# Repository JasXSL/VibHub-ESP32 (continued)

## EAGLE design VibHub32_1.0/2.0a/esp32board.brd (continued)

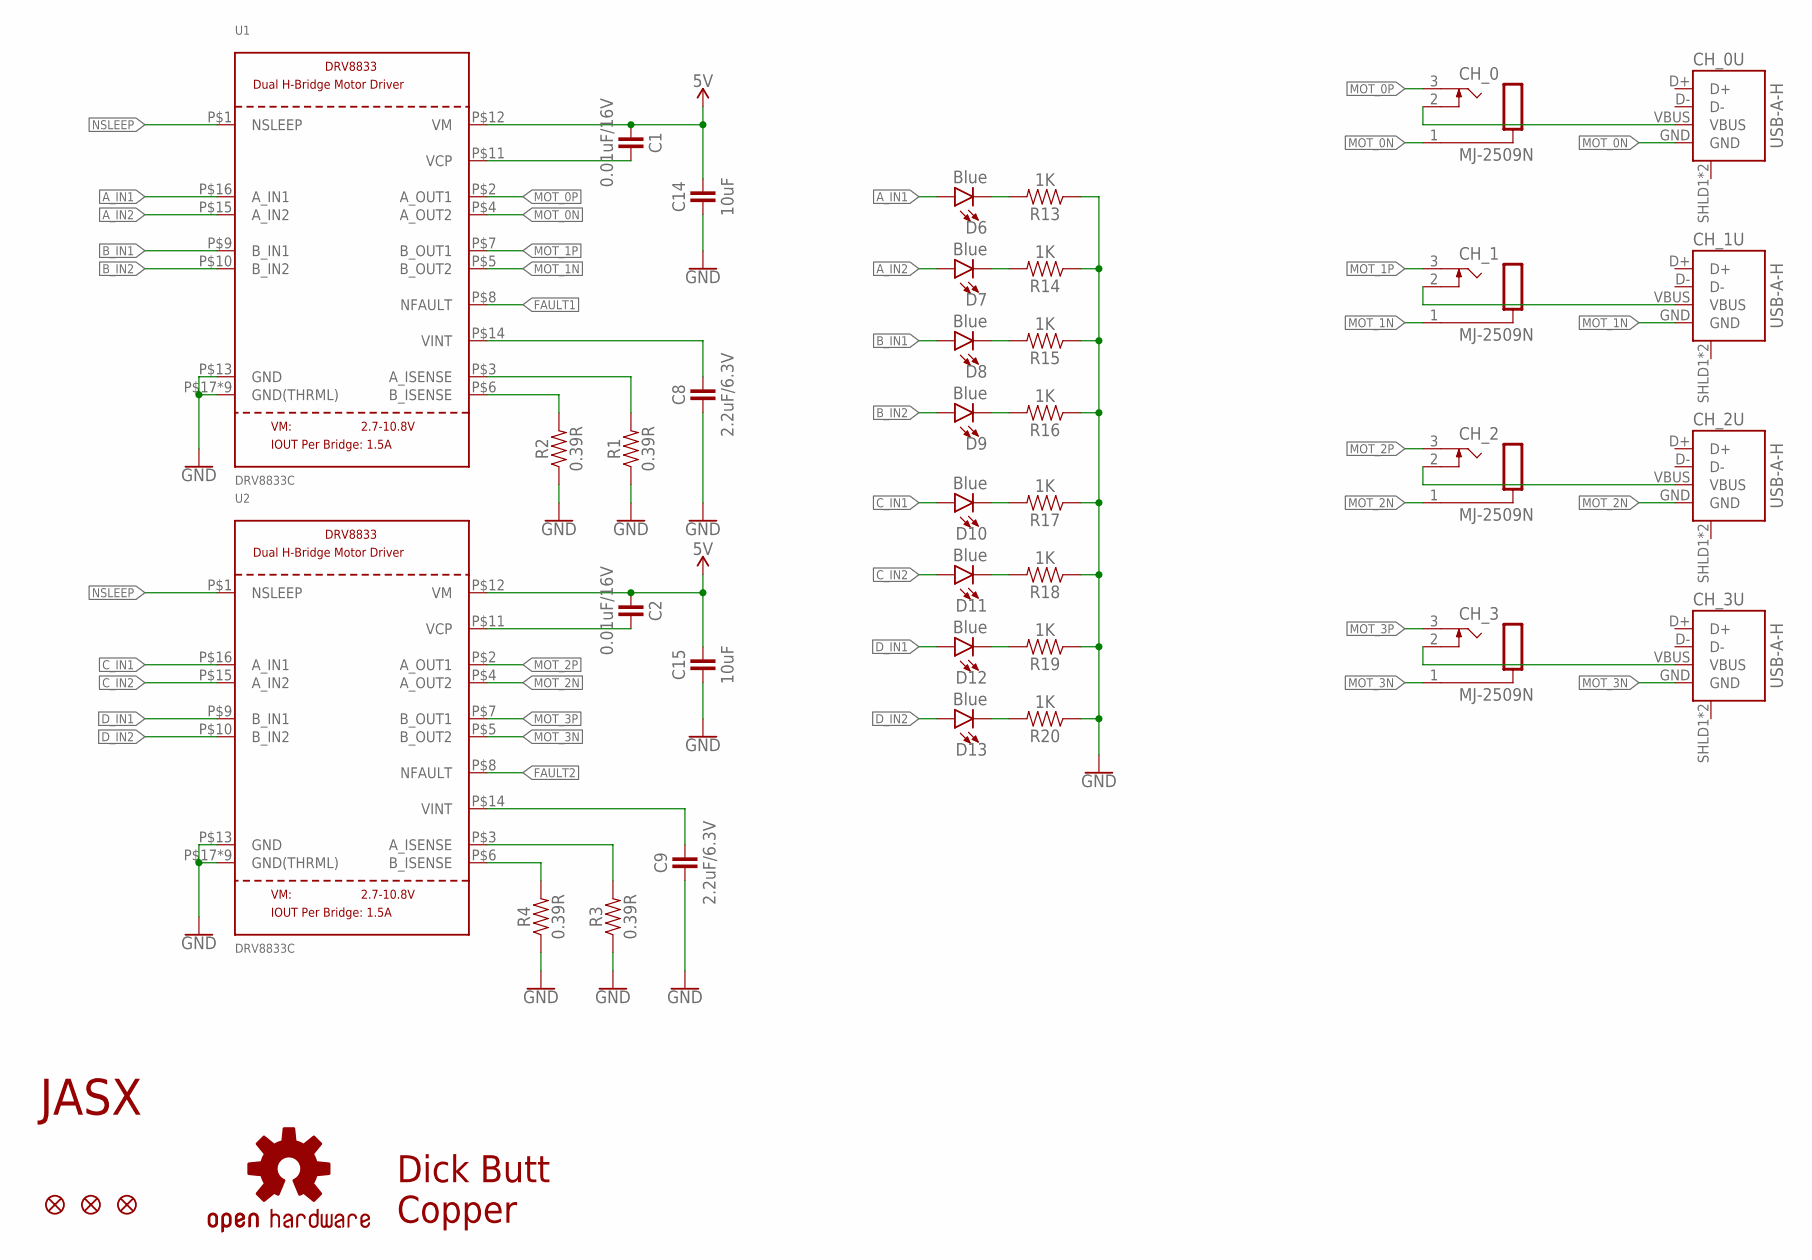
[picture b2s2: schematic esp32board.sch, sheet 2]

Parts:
C1, C2: 0.01uF/16V; C0805
C8, C9: 2.2uF/6.3V; C0805
C14, C15: 10uF; C0805
CH_0, CH_1, CH_2, CH_3: MJ-2509N
CH_0U, CH_1U, CH_2U, CH_3U: USB-A-H
D6, D7, D8, D9, D10, D11, D12, D13: Blue; CHIPLED_0805
FD1, FD2, FD3: FIDUCIAL1X2; FIDUCIAL-1X2
LOGO1: OSHW-LOGOM; OSHW-LOGO-M
LOGO2: JASX_LOGO_MID; JASX_LOGO_M
LOGO3: DICKBUTTCOPPER; DICKBUTT_COPPER
R1, R2, R3, R4: 0.39R; 0805
R13, R14, R15, R16, R17, R18, R19, R20: 1K; 0805
U1, U2: DRV8833C; HTSSOP16

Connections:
5V: C1.1, C2.1, C14.2, C15.2, U1.P$12 (VM), U2.P$12 (VM); also elsewhere on the board
A_IN1: D6.A, U1.P$16 (A_IN1); also elsewhere on the board
A_IN2: D7.A, U1.P$15 (A_IN2); also elsewhere on the board
A_ISENSE0: R1.2, U1.P$3 (A_ISENSE)
A_ISENSE1: R3.2, U2.P$3 (A_ISENSE)
B_IN1: D8.A, U1.P$9 (B_IN1); also elsewhere on the board
B_IN2: D9.A, U1.P$10 (B_IN2); also elsewhere on the board
B_ISENSE0: R2.2, U1.P$6 (B_ISENSE)
B_ISENSE1: R4.2, U2.P$6 (B_ISENSE)
C_IN1: D10.A, U2.P$16 (A_IN1); also elsewhere on the board
C_IN2: D11.A, U2.P$15 (A_IN2); also elsewhere on the board
D_IN1: D12.A, U2.P$9 (B_IN1); also elsewhere on the board
D_IN2: D13.A, U2.P$10 (B_IN2); also elsewhere on the board
FAULT1: U1.P$8 (NFAULT); also elsewhere on the board
FAULT2: U2.P$8 (NFAULT); also elsewhere on the board
GND: C8.1, C9.1, C14.1, C15.1, R1.1, R2.1, R3.1, R4.1, R13.1, R14.1, R15.1, R16.1, R17.1, R18.1, R19.1, R20.1, U1.P$13 (GND), U1.P$17 (GND(THRML)), U1.P$18 (GND(THRML)), U1.P$19 (GND(THRML)), U1.P$20 (GND(THRML)), U1.P$21 (GND(THRML)), U1.P$22 (GND(THRML)), U1.P$23 (GND(THRML)), U1.P$24 (GND(THRML)), U1.P$25 (GND(THRML)), U2.P$13 (GND), U2.P$17 (GND(THRML)), U2.P$18 (GND(THRML)), U2.P$19 (GND(THRML)), U2.P$20 (GND(THRML)), U2.P$21 (GND(THRML)), U2.P$22 (GND(THRML)), U2.P$23 (GND(THRML)), U2.P$24 (GND(THRML)), U2.P$25 (GND(THRML)); also elsewhere on the board
MOT_0N: CH_0.1 (S), CH_0U.GND, U1.P$4 (A_OUT2)
MOT_0P: CH_0.3 (T), U1.P$2 (A_OUT1)
MOT_1N: CH_1.1 (S), CH_1U.GND, U1.P$5 (B_OUT2)
MOT_1P: CH_1.3 (T), U1.P$7 (B_OUT1)
MOT_2N: CH_2.1 (S), CH_2U.GND, U2.P$4 (A_OUT2)
MOT_2P: CH_2.3 (T), U2.P$2 (A_OUT1)
MOT_3N: CH_3.1 (S), CH_3U.GND, U2.P$5 (B_OUT2)
MOT_3P: CH_3.3 (T), U2.P$7 (B_OUT1)
unnamed: D6.C, R13.2
unnamed: D7.C, R14.2
unnamed: D8.C, R15.2
unnamed: D9.C, R16.2
unnamed: D10.C, R17.2
unnamed: D11.C, R18.2
unnamed: D12.C, R19.2
unnamed: D13.C, R20.2
unnamed: CH_3.2 (TS), CH_3U.VBUS
unnamed: CH_0.2 (TS), CH_0U.VBUS
unnamed: CH_1.2 (TS), CH_1U.VBUS
unnamed: CH_2.2 (TS), CH_2U.VBUS
NSLEEP: U1.P$1 (NSLEEP), U2.P$1 (NSLEEP); also elsewhere on the board
VCP0: C1.2, U1.P$11 (VCP)
VCP1: C2.2, U2.P$11 (VCP)
VINT0: C8.2, U1.P$14 (VINT)
VINT1: C9.2, U2.P$14 (VINT)

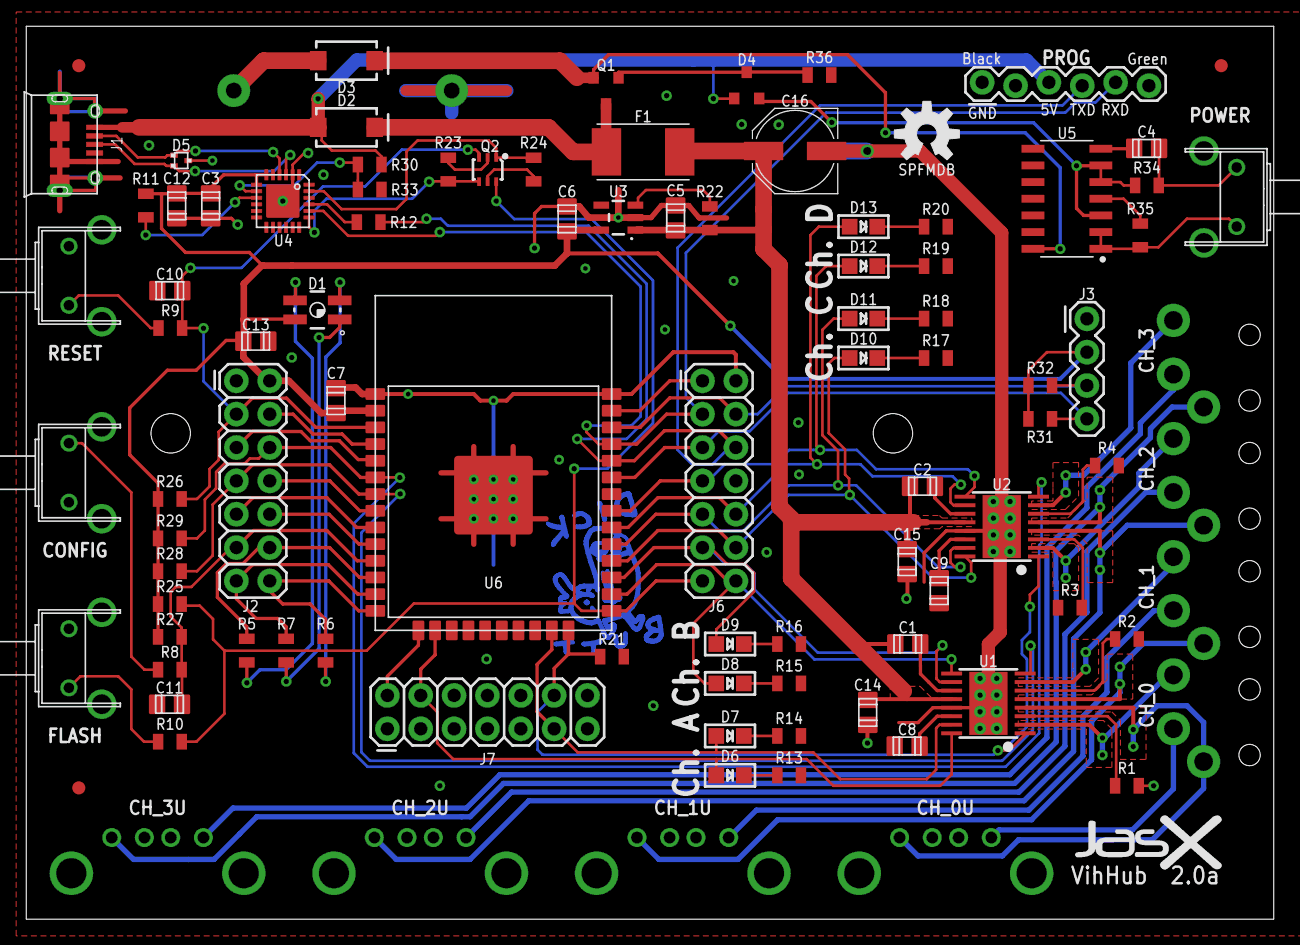
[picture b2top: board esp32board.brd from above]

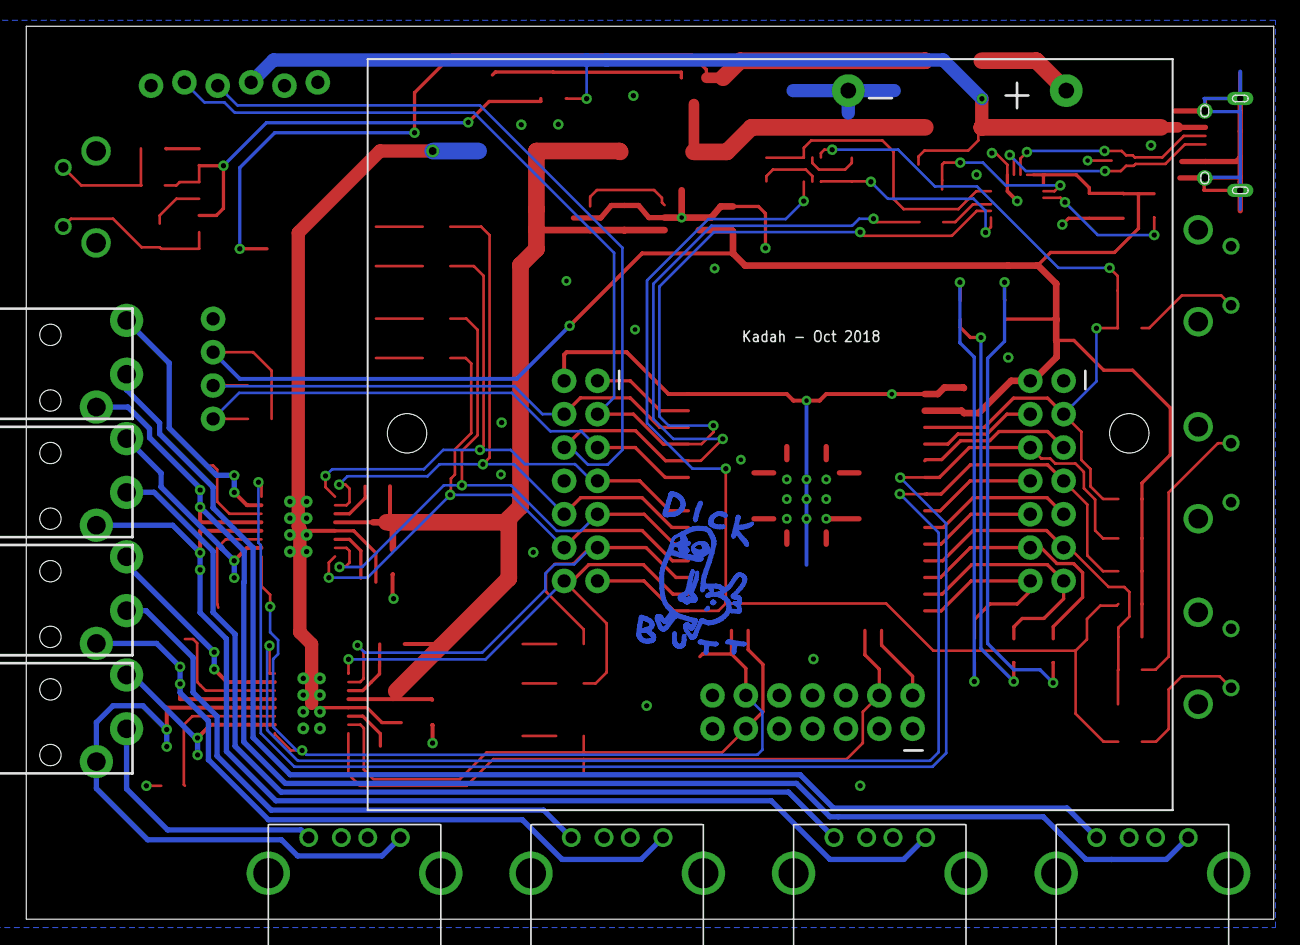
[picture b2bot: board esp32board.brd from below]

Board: 2 copper layers, 95.0 x 68.0 mm, 99 parts (10 on the bottom side), 83 nets.

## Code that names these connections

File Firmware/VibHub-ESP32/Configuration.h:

/*
    This is the project configuration, these values don't change
*/
#ifndef _VH_CONFIGURATION
#define _VH_CONFIGURATION
#include <FS.h>
#include <Arduino.h>
// Bug with arduino unless I undefine these
#undef min
#undef max


// Capabilities
#define CTASK_PWM_BASIC "p"                     // Capable of handling motor updates in one go
#define CTASK_PWM_SPECIFIC "ps"                 // Capable of handling individual motor updates
#define CTASK_PROGRAMS "vib"                    // Capable of handling programs
#define CTASK_APP_OFFLINE "app_offline"         // Capable of doing something when app goes offline
#define CTASK_CUSTOM_TO_DEVICE "dCustom"        // Capable of receiving custom data from the app
#define CTASK_DEVICE_TO_CUSTOM "aCustom"        // Capable of sending custom data to the app
class Capability{
    public:
        Capability( char* t, bool modded = false ){
            type = t;
            modified = modded;            
        }
        char *type;
        bool modified;
};


namespace Configuration{

    const char VH_VERSION[]         = "0.3.1";          // Software version
    const char VH_HWVERSION[]       = "ESP32_2.1";      // Hardware type & version
    const char WIFI_SSID[]          = "VibHub";         // Network SSID
    const char DEFAULT_HOST[]       = "vibhub.io";      // Default socket host
    const int  DEFAULT_PORT         = 443;               // Default socket port
    const char API_URL[]            = "/socket.io/?transport=websocket";
    const char SETTINGS_FILE[]      = "/config.json";   // Default SPIFFS config file

    // Metadata
    const uint8_t NUM_MOTORS        = 4;
    const uint8_t NR_CAPABILITIES   = 3;
    const Capability CAPABILITIES[NR_CAPABILITIES] = {
        Capability(CTASK_PWM_BASIC),
        Capability(CTASK_PWM_SPECIFIC),
        Capability(CTASK_PROGRAMS)
    };

    // Websockets
    const int WEBSOCKET_RECONNECT_TIME = 3000;          // How long to wait after a connection failed

    // Status LED
    const uint8_t SLED_BRIGHTNESS   = 50;   // Status LED brightness, 0-255

    // ESP32 2.0a/2.1 Board GPIO Assignments
    const uint8_t PIN_SLED_R        = 14;   // GPIO pin for RGB (inverse, a PWM of 255 turns off)
    const uint8_t PIN_SLED_G        = 12;
    const uint8_t PIN_SLED_B        = 27;
    const uint8_t PIN_SLED2_R       = 32;   // 2.1 only
    const uint8_t PIN_SLED2_G       = 33;   // 2.1 only
    const uint8_t PIN_SLED2_B       = 25;   // 2.1 only
    const uint8_t PIN_CONFIG_BUTTON = 26;   // Configuration pin. Use a pull-up resistor
    const uint8_t PIN_NSLEEP        = 2;    // Disables motor drivers when low
    const uint8_t PIN_MOTOR_A_IN1   = 13;
    const uint8_t PIN_MOTOR_A_IN2   = 15;
    const uint8_t PIN_MOTOR_B_IN1   = 4;
    const uint8_t PIN_MOTOR_B_IN2   = 16;
    const uint8_t PIN_MOTOR_C_IN1   = 17;
    const uint8_t PIN_MOTOR_C_IN2   = 5;
    const uint8_t PIN_MOTOR_D_IN1   = 19;
    const uint8_t PIN_MOTOR_D_IN2   = 18;
    const uint8_t PIN_MOTOR_FAULT1  = 35;   // Currently unused
    const uint8_t PIN_MOTOR_FAULT2  = 34;   // Currently unused
    const uint8_t PIN_SDA           = 21;   // Currently unused
    const uint8_t PIN_SCL           = 22;   // Currently unused
    const uint8_t PIN_POWEROFF      = 23;   // Signal high turns off main power
    

    // PWM
    const int PWM_FREQ              = 12000; // PWM Frequency
    const int PWM_RESOLUTION        = 8;     // PWM resolution

    // Button config
    const bool BUTTON_UP            = HIGH;  // Value when the button is not pressed
    const bool BUTTON_DOWN          = LOW;   // Value when the button IS pressed
    const int BUTTON_HOLD_TIME      = 4000;  // Time before it enters config mode
    const uint8_t BUTTON_DEBOUNCE   = 100;   // Debounce time


    // Global randomizer function
    // Returns a random value which can be min through and including max
    // min0 max3 would generate 0, 1, 2, or 3
    inline int espRandBetween(int minimum, int maximum){
        float r = (float)esp_random()/UINT32_MAX;
        return (minimum+floor((maximum+1-minimum)*r));
    }

    const char ROOTCA[] = \
        "-----BEGIN CERTIFICATE-----\n" \
        "MIIFFjCCAv6gAwIBAgIRAJErCErPDBinU/bWLiWnX1owDQYJKoZIhvcNAQELBQAw\n" \
        "TzELMAkGA1UEBhMCVVMxKTAnBgNVBAoTIEludGVybmV0IFNlY3VyaXR5IFJlc2Vh\n" \
        "cmNoIEdyb3VwMRUwEwYDVQQDEwxJU1JHIFJvb3QgWDEwHhcNMjAwOTA0MDAwMDAw\n" \
        "WhcNMjUwOTE1MTYwMDAwWjAyMQswCQYDVQQGEwJVUzEWMBQGA1UEChMNTGV0J3Mg\n" \
        "RW5jcnlwdDELMAkGA1UEAxMCUjMwggEiMA0GCSqGSIb3DQEBAQUAA4IBDwAwggEK\n" \
        "AoIBAQC7AhUozPaglNMPEuyNVZLD+ILxmaZ6QoinXSaqtSu5xUyxr45r+XXIo9cP\n" \
        "R5QUVTVXjJ6oojkZ9YI8QqlObvU7wy7bjcCwXPNZOOftz2nwWgsbvsCUJCWH+jdx\n" \
        "sxPnHKzhm+/b5DtFUkWWqcFTzjTIUu61ru2P3mBw4qVUq7ZtDpelQDRrK9O8Zutm\n" \
        "NHz6a4uPVymZ+DAXXbpyb/uBxa3Shlg9F8fnCbvxK/eG3MHacV3URuPMrSXBiLxg\n" \
        "Z3Vms/EY96Jc5lP/Ooi2R6X/ExjqmAl3P51T+c8B5fWmcBcUr2Ok/5mzk53cU6cG\n" \
        "/kiFHaFpriV1uxPMUgP17VGhi9sVAgMBAAGjggEIMIIBBDAOBgNVHQ8BAf8EBAMC\n" \
        "AYYwHQYDVR0lBBYwFAYIKwYBBQUHAwIGCCsGAQUFBwMBMBIGA1UdEwEB/wQIMAYB\n" \
        "Af8CAQAwHQYDVR0OBBYEFBQusxe3WFbLrlAJQOYfr52LFMLGMB8GA1UdIwQYMBaA\n" \
        "FHm0WeZ7tuXkAXOACIjIGlj26ZtuMDIGCCsGAQUFBwEBBCYwJDAiBggrBgEFBQcw\n" \
        "AoYWaHR0cDovL3gxLmkubGVuY3Iub3JnLzAnBgNVHR8EIDAeMBygGqAYhhZodHRw\n" \
        "Oi8veDEuYy5sZW5jci5vcmcvMCIGA1UdIAQbMBkwCAYGZ4EMAQIBMA0GCysGAQQB\n" \
        "gt8TAQEBMA0GCSqGSIb3DQEBCwUAA4ICAQCFyk5HPqP3hUSFvNVneLKYY611TR6W\n" \
        "PTNlclQtgaDqw+34IL9fzLdwALduO/ZelN7kIJ+m74uyA+eitRY8kc607TkC53wl\n" \
        "ikfmZW4/RvTZ8M6UK+5UzhK8jCdLuMGYL6KvzXGRSgi3yLgjewQtCPkIVz6D2QQz\n" \
        "CkcheAmCJ8MqyJu5zlzyZMjAvnnAT45tRAxekrsu94sQ4egdRCnbWSDtY7kh+BIm\n" \
        "lJNXoB1lBMEKIq4QDUOXoRgffuDghje1WrG9ML+Hbisq/yFOGwXD9RiX8F6sw6W4\n" \
        "avAuvDszue5L3sz85K+EC4Y/wFVDNvZo4TYXao6Z0f+lQKc0t8DQYzk1OXVu8rp2\n" \
        "yJMC6alLbBfODALZvYH7n7do1AZls4I9d1P4jnkDrQoxB3UqQ9hVl3LEKQ73xF1O\n" \
        "yK5GhDDX8oVfGKF5u+decIsH4YaTw7mP3GFxJSqv3+0lUFJoi5Lc5da149p90Ids\n" \
        "hCExroL1+7mryIkXPeFM5TgO9r0rvZaBFOvV2z0gp35Z0+L4WPlbuEjN/lxPFin+\n" \
        "HlUjr8gRsI3qfJOQFy/9rKIJR0Y/8Omwt/8oTWgy1mdeHmmjk7j1nYsvC9JSQ6Zv\n" \
        "MldlTTKB3zhThV1+XWYp6rjd5JW1zbVWEkLNxE7GJThEUG3szgBVGP7pSWTUTsqX\n" \
        "nLRbwHOoq7hHwg==\n" \
        "-----END CERTIFICATE-----";
};



#endif

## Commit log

2018-08-23 Initial commit
    Motor driver is still missing. Can't get portal to work either.
2018-08-23 Fix for RGB LED
2018-08-23 Comments
2018-08-23 WiFiTest
2018-08-24 Adds motor stuff. Instant sets work, but programs crash the ESP at line 89 of Motor.cpp
2018-08-25 ITWERKS - Mapped up the rest of the motors - The whole thing at least runs now. Time for improvements
2018-08-25 - Add hardware RNG. - Add wifi error handler
2018-08-25 Formatting
2018-08-25 Re-implemented DRV8833 features Renamed pin and pwm variables to match DRV8833's input names Added details from data sheet about decay modes
2018-08-25 Added output enable/disable back to ApiClient
2018-08-26 Added initial OTA support (see comments #2) Renamed pin defines for motors to match driver input names
2018-08-27 First stab at a manual
2018-08-28 Tweening 2 test added
2018-08-29 Unit tests - Program resets added so you can keep one program object per motor - Added missing easing types
2018-08-29 Memory test
2018-08-29 Implement the new tweening
2018-08-29 Set tween program to completed at initialization to prevent PWM updates while nothing is running
2018-08-29 remove a debug thing
2018-10-22 Added 1.0 board and config
2018-10-22 Updated comments on config
2018-10-23 Added board test sketch
2019-01-14 Add bluetooth. Can send P calls, but not programs yet.
2019-01-15 hook up programs to bluetooth
2019-01-16 For testing, bluetooth bonding is now enabled after 30 sec, then disabled after bonding
2019-01-17 Make bluetooth pairing toggleable by holding the config button
2019-01-17 Added bluetooth enable to captive portal
2019-01-17 Forgot to disable bluetooth settings while bluetooth is disabled
2019-01-17 Allow VH to run with bluetooth and no wifi
2019-01-18 Implement sleep timeout
2019-01-18 disable bluetooth by default
2019-02-02 Make wifi save regardless of if credentials are proper. Because bluetooth.
2019-02-02 Only force reboot if BT was just enabled when saving settings.
2019-02-02 fix bluetooth config flash
2019-02-05 Updates to Bluetooth
2019-02-05 Make bluetooth be enabled by default, but enter config mode until the first save Restart after changing WiFi settings
2019-07-22 Added case STLs
2019-07-22 Added experimental v0.2.1 firmware
2019-07-22 Shorten wifimanager
2019-07-22 Upgrade to ArduinoJSON6
2019-07-24 Fix for clicking the WHOLE button. That's 60% more button per button!
2019-07-28 Added SSL support
2019-08-01 Catch crash on bad program
2019-08-01 Wait for longer for WiFi Update to connect to official VibHub SSL default
2019-08-01 fix copying
2019-08-02 Added task
2019-08-02 Fix compiler warning
2019-08-02 Compile warnings fixes
2019-08-02 Added NTP time set on wifi connect, likely unneeded
2019-08-02 Removed old test code
2019-08-04 Forked socket.io-client library Updated library links comment
2019-08-04 Added some eagle project file ignores
2019-08-04 Moved sketch to sub folder
2019-08-04 Moved board test sketch
2019-08-04 Ignore local testing folder
2019-08-05 Seems to have slightly better mem use
2019-08-07 Moved 2.0a board files to subfolder
2019-08-08 Add a bit of typechecking
2019-09-14 Remove bluetooth
2019-10-20 Make forward rotation preferred
2019-10-23 Lower PWM freq and reverse port order
2019-10-23 LEDC didn't like low freq :< set it to 5khz
2019-12-24 Added second LED and updates for 2.1 board
2019-12-24 Add SPIFFS format sketch
2019-12-24 Updated board tester sketch
2019-12-27 Added hardware info printouts to test sketch
2020-01-12 Fixed unable to set PWM duty cycle to 100% (256)
2020-03-05 Update ignores
2020-03-05 Added files for 2.1c board rev Added board test for 2.1b+ Update format sketch
2020-03-05 Missing changes from last commit
2020-03-06 BOM consolidation Removed 150K 0805 res requirement
2020-03-06 Unsaved changes from last commit
2020-05-19 Updated BOM
2020-05-19 Added 2.1 case STLs
2020-05-19 Fixed silkscreen on D1 and D5
2020-05-19 Added LCSL BOM file (BOM tool kinda works)
2020-05-22 Added tighter battery cover (negative tolerance) Added 2 variants of the top with inner logo closer to the front face (0.2mm vs 0.4mm)
2021-03-01 bump version
2021-03-02 errant include
2021-03-12 Added schematic pngs
2022-04-14 Remove .vscode dir
2022-04-14 Updated tests for newer esptool version
2022-04-14 Added platformio support Fixed various compile issues Fixed custom head extension construction Removed outdated Ticker-esp32 depend Updated external lib list Updated .gitignore for vscode
2022-04-14 Added .vscode/extensions.json
